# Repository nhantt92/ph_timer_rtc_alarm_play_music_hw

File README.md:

# ph_timer_rtc_alarm_play_music_hw
ph_timer_rtc_alarm_play_music_hw

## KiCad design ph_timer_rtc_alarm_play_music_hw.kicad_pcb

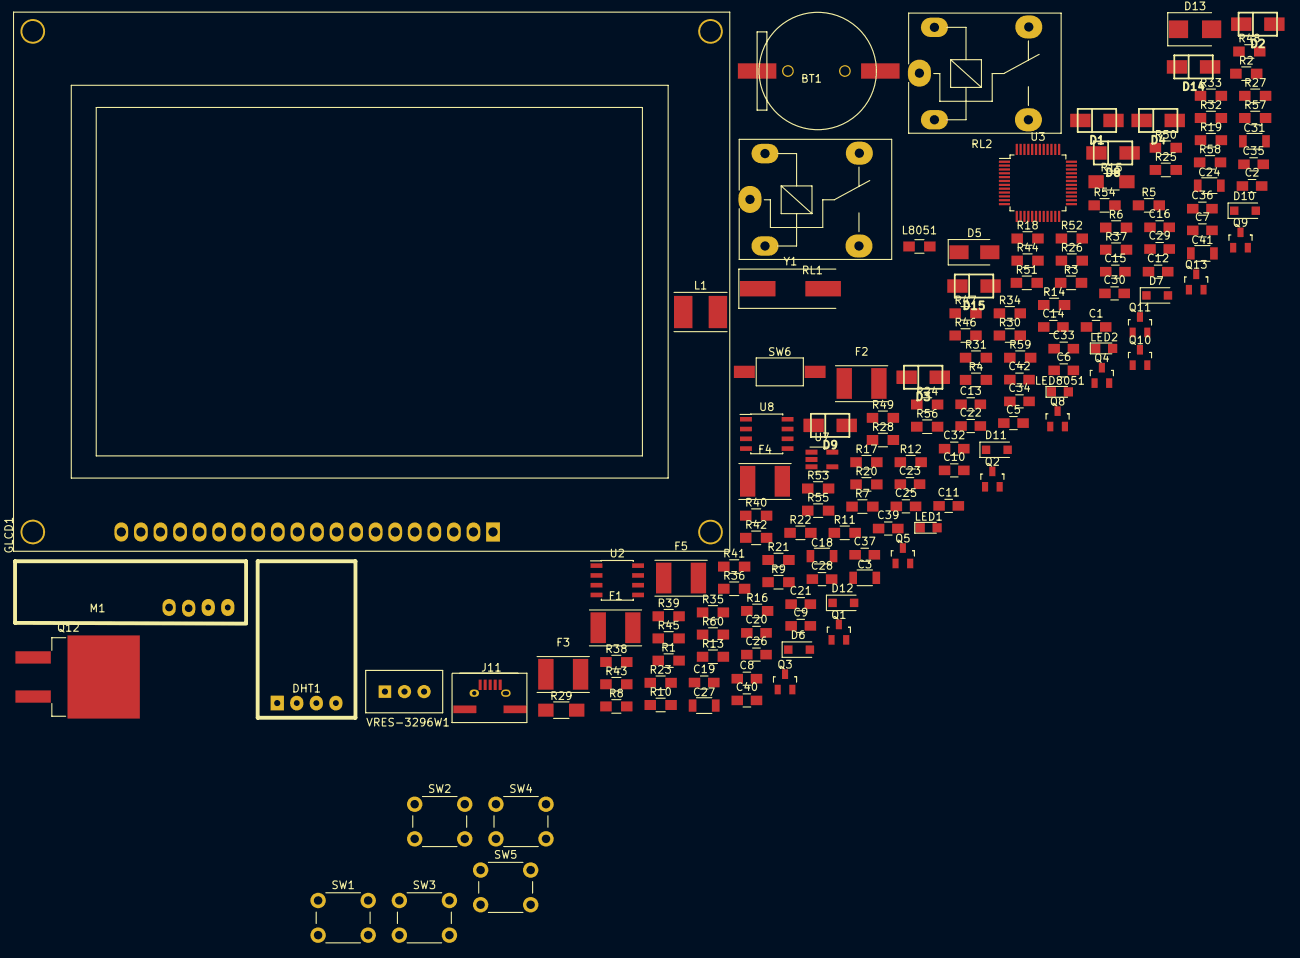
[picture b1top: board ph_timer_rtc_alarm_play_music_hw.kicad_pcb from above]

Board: 2 copper layers, 154 parts (0 on the bottom side), 75 nets, no tracks yet.

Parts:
BT1: BT_CR1220_S; BT_CR1220
C1, C2, C5, C6, C8, C9, C10, C11, C14, C15, C16, C19, C20, C21, C22, C23, C26, C28, C30, C32, C35, C37, C39, C40, C42: 100nF; C_0805_HandSoldering
C3, C18, C24, C27, C31, C41: 10uF; C_1206
C7: 33pF; C_0805_HandSoldering
C12, C13: 20pF; C_0805_HandSoldering
C25, C29, C34: 1uF; C_0805_HandSoldering
C33: 47nF; C_0805_HandSoldering
C36: 22nF; C_0805_HandSoldering
D1, D14, D15: D_TVS; DO-214AC(SMA)
D2, D3, D4, D8, D9: 1N4007_M7; DO-214AC(SMA)
D5: SS24_SMA; D_SMA
D6, D7: 12V/SOD123; D_SOD-123F
D10: 1N4148_T4; D_SOD-123F
D11: 12V_SOD123; D_SOD-123F
D12: 1N4007_T7; D_SOD-123F
D13: SS5x_SMB; D_SMB
DHT1: DHT22; DHT11
F1, F4, F5: FusePTC; Fuse_SMD1812
F2, F3: 24V/1A; Fuse_SMD1812
GLCD1: GLCD_ST7920
J11: USB_B_Micro; USB-Micro-B
L1: 100uH_5D28; L_5D28_HandSoldering
L8051: 30R; L_0805_HandSoldering
LED1, LED2, LED8051: LED0805; LED_0805
M1: RF315; RF_YKTR-5S
Q1, Q2, Q3, Q4, Q5, Q8, Q9, Q11, Q13: C1815_SOT23; SOT-23
Q10: A1015_SOT23; SOT-23
Q12: IRF3205_N_D2PAK; TO-263-2Lead
R1, R4, R7, R8, R10, R13, R31, R32, R33, R34, R45, R50, R52, R53, R56, R57: 10k; R_0805_HandSoldering
R2, R11, R12, R23, R24, R25, R28, R44, R47, R48, R54: 2.2k; R_0805_HandSoldering
R3, R14, R26, R37, R38, R49: 1k; R_0805_HandSoldering
R5, R6, R27: 0R; R_0805_HandSoldering
R9, R16: 220R; R_0805_HandSoldering
R15, R29: 0.15R; R_1206_HandSoldering
R17, R20: 4.7K; R_0805_HandSoldering
R18: 1k/1%; R_0805_HandSoldering
R19, R21: 10K; R_0805_HandSoldering
R22: 3k/1%; R_0805_HandSoldering
R30: 1K; R_0805_HandSoldering
R35, R36, R51: 10R; R_0805_HandSoldering
R39: 1.5K; R_0805_HandSoldering
R40, R41: 22R; R_0805_HandSoldering
R42: 100R; R_0805_HandSoldering
R43, R55: 4.7k; R_0805_HandSoldering
R46: 51R; R_0805_HandSoldering
R58, R60: 20k; R_0805_HandSoldering
R59: 120R; R_0805_HandSoldering
RL1, RL2: G5Q-1; Relay_SRD-SONGLE
SW1, SW2, SW3, SW4, SW5: SW_Push; SW_PUSH_6mm_h8.5mm
SW6: SW_Push; Button_SW_2PIN
U2: MC34063; SOIC-8_3.9x4.9mm_Pitch1.27mm
U3: STM32F103CBT6; LQFP-48_7x7mm_Pitch0.5mm
U7: RT9193-33GB; SOT-23-5_HandSoldering
U8: MAX485_SMD; SOIC-8_3.9x4.9mm_Pitch1.27mm
VRES-3296W1: VRES-3296W
Y1: 8Mhz; Crystal_HC49-S

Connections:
+3V3: C16.1, C18.1, C20.2, C21.2, C22.2, C23.2, C28.1, C39.1, DHT1.1, L8051.1, R1.1, R4.1, R7.1, R10.1, R13.1, R16.1, R17.1, R20.1, R21.1, R23.2, R24.2, R43.1, U3.24, U3.36, U3.48, U7.5
+5V: C19.1, C40.2, D10.1, D12.1, L1.2, R5.1, R22.2, R29.1, R56.2, R57.2, R58.2, U8.8
+24V: C6.1, D2.1, D3.1, D4.1, D8.1, D9.1, D13.1, F2.1, F3.1, R15.1, R31.1, R33.1, R45.2, R50.2, RL1.5, RL2.5, U2.6
/485_RX: R53.1, R55.1, U3.31
/485_TX: R54.1, U3.30
/BT1: C1.1, R1.2, SW1.1, U3.18
/BT2: C2.1, R4.2, SW2.1, U3.19
/BT3: C5.1, R7.2, SW3.1, U3.20
/BT4: C9.1, R10.2, SW4.1, U3.39
/BT5: C10.1, R13.2, SW5.1, U3.40
/BUZZER: R48.1, U3.28
/DHT22: DHT1.2, R43.2, U3.10
/LED_STT: LED1.1, U3.2
/PWM: R44.2, U3.46
/RF315: C33.2, R46.1, U3.29
/RL1: R2.1, U3.25, U3.41
/SCL: R17.2, U3.42
/SDA: R20.2, U3.43
/USB_DIS: R39.2, U3.38
/USB_DM: R41.2, U3.32
/USB_DP: R40.2, U3.33
/ctrl1: R24.1, R28.2, U3.26
/ctrl2: R23.1, R25.2, U3.27
BAT+: C11.1, C27.1, C29.1, C30.2, C31.2, C32.2, C34.1, C35.1, C37.2, C41.2, C42.2, M1.1, R6.1, R9.2, R42.1, R52.2, U7.1, VRES-3296W1.1
GND: BT1.2, C1.2, C2.2, C3.2, C5.2, C6.2, C7.2, C8.1, C9.2, C10.2, C11.2, C12.1, C13.1, C14.2, C15.1, C16.2, C18.2, C19.2, C20.1, C21.1, C22.1, C23.1, C24.2, C25.1, C26.1, C27.2, C28.2, C30.1, C31.1, C32.1, C33.1, C34.2, C35.2, C36.2, C37.1, C39.2, C40.1, C41.1, C42.1, D1.2, D5.2, D6.2, D7.2, D11.2, D14.1, D15.2, DHT1.4, GLCD1.1, J11.5, J11.6, M1.4, Q1.2, Q2.2, Q3.2, Q4.2, Q5.2, Q8.2, Q10.2, Q11.2, Q12.3, Q13.2, R3.2, R8.2, R14.2, R18.2, R19.2, R27.2, R30.2, R32.2, R34.2, R49.1, R53.2, R60.1, SW1.2, SW2.2, SW3.2, SW4.2, SW5.2, SW6.1, U2.4, U3.8, U3.23, U3.35, U3.47, U7.2, U8.4, U8.5, VRES-3296W1.3
unnamed: BT1.1, C14.1, U3.1
unnamed: C3.1, C8.2, GLCD1.2, R5.2, R6.2
unnamed: C7.1, U2.3
unnamed: C12.2, U3.5, Y1.1
unnamed: C13.2, U3.6, Y1.2
unnamed: C15.2, R21.2, SW6.2, U3.7
unnamed: C24.1, LED2.2, LED8051.2, R26.1, R29.2
unnamed: C25.2, C26.2, L8051.2, U3.9
unnamed: C36.1, U7.4
unnamed: D1.1, D2.2, F1.2
unnamed: D3.2, Q1.3, RL1.2
unnamed: D4.2, Q3.3, RL2.2
unnamed: D5.1, L1.1, U2.2
unnamed: D6.1, Q4.3, R31.2, R32.1, R35.1
unnamed: D7.1, Q5.3, R33.2, R34.1, R36.1
unnamed: D10.2, J11.1
unnamed: D11.1, Q9.2, Q10.3, R51.1
unnamed: D12.2, Q11.3
unnamed: D13.2, Q12.2
unnamed: D14.2, F4.1, R58.1, R59.2, U8.6
unnamed: D15.1, F5.1, R59.1, R60.2, U8.7
unnamed: GLCD1.3, VRES-3296W1.2
unnamed: GLCD1.15, R8.1
unnamed: GLCD1.19, R9.1
unnamed: GLCD1.20, Q2.3
unnamed: J11.2, R41.1
unnamed: J11.3, R39.1, R40.1
unnamed: LED1.2, R16.2
unnamed: LED2.1, R38.1
unnamed: LED8051.1, R37.1
unnamed: M1.2, M1.3, R46.2
unnamed: Q1.1, R2.2, R3.1
unnamed: Q2.1, R11.1
unnamed: Q3.1, R12.2, R14.1
unnamed: Q4.1, R25.1
unnamed: Q5.1, R28.1
unnamed: Q8.1, R44.1
unnamed: Q8.3, R45.1, R47.1
unnamed: Q9.3, R50.1
unnamed: Q9.1, Q10.1, R47.2
unnamed: Q11.1, R48.2
unnamed: Q12.1, R51.2
unnamed: Q13.1, R54.2
unnamed: Q13.3, R57.1, U8.2, U8.3
unnamed: R15.2, U2.1, U2.7, U2.8
unnamed: R18.1, R22.1, U2.5
unnamed: R19.1, U3.44
unnamed: R26.2, R27.1
unnamed: R52.1, U7.3
unnamed: R55.2, R56.1, U8.1

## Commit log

2020-02-15 init project
